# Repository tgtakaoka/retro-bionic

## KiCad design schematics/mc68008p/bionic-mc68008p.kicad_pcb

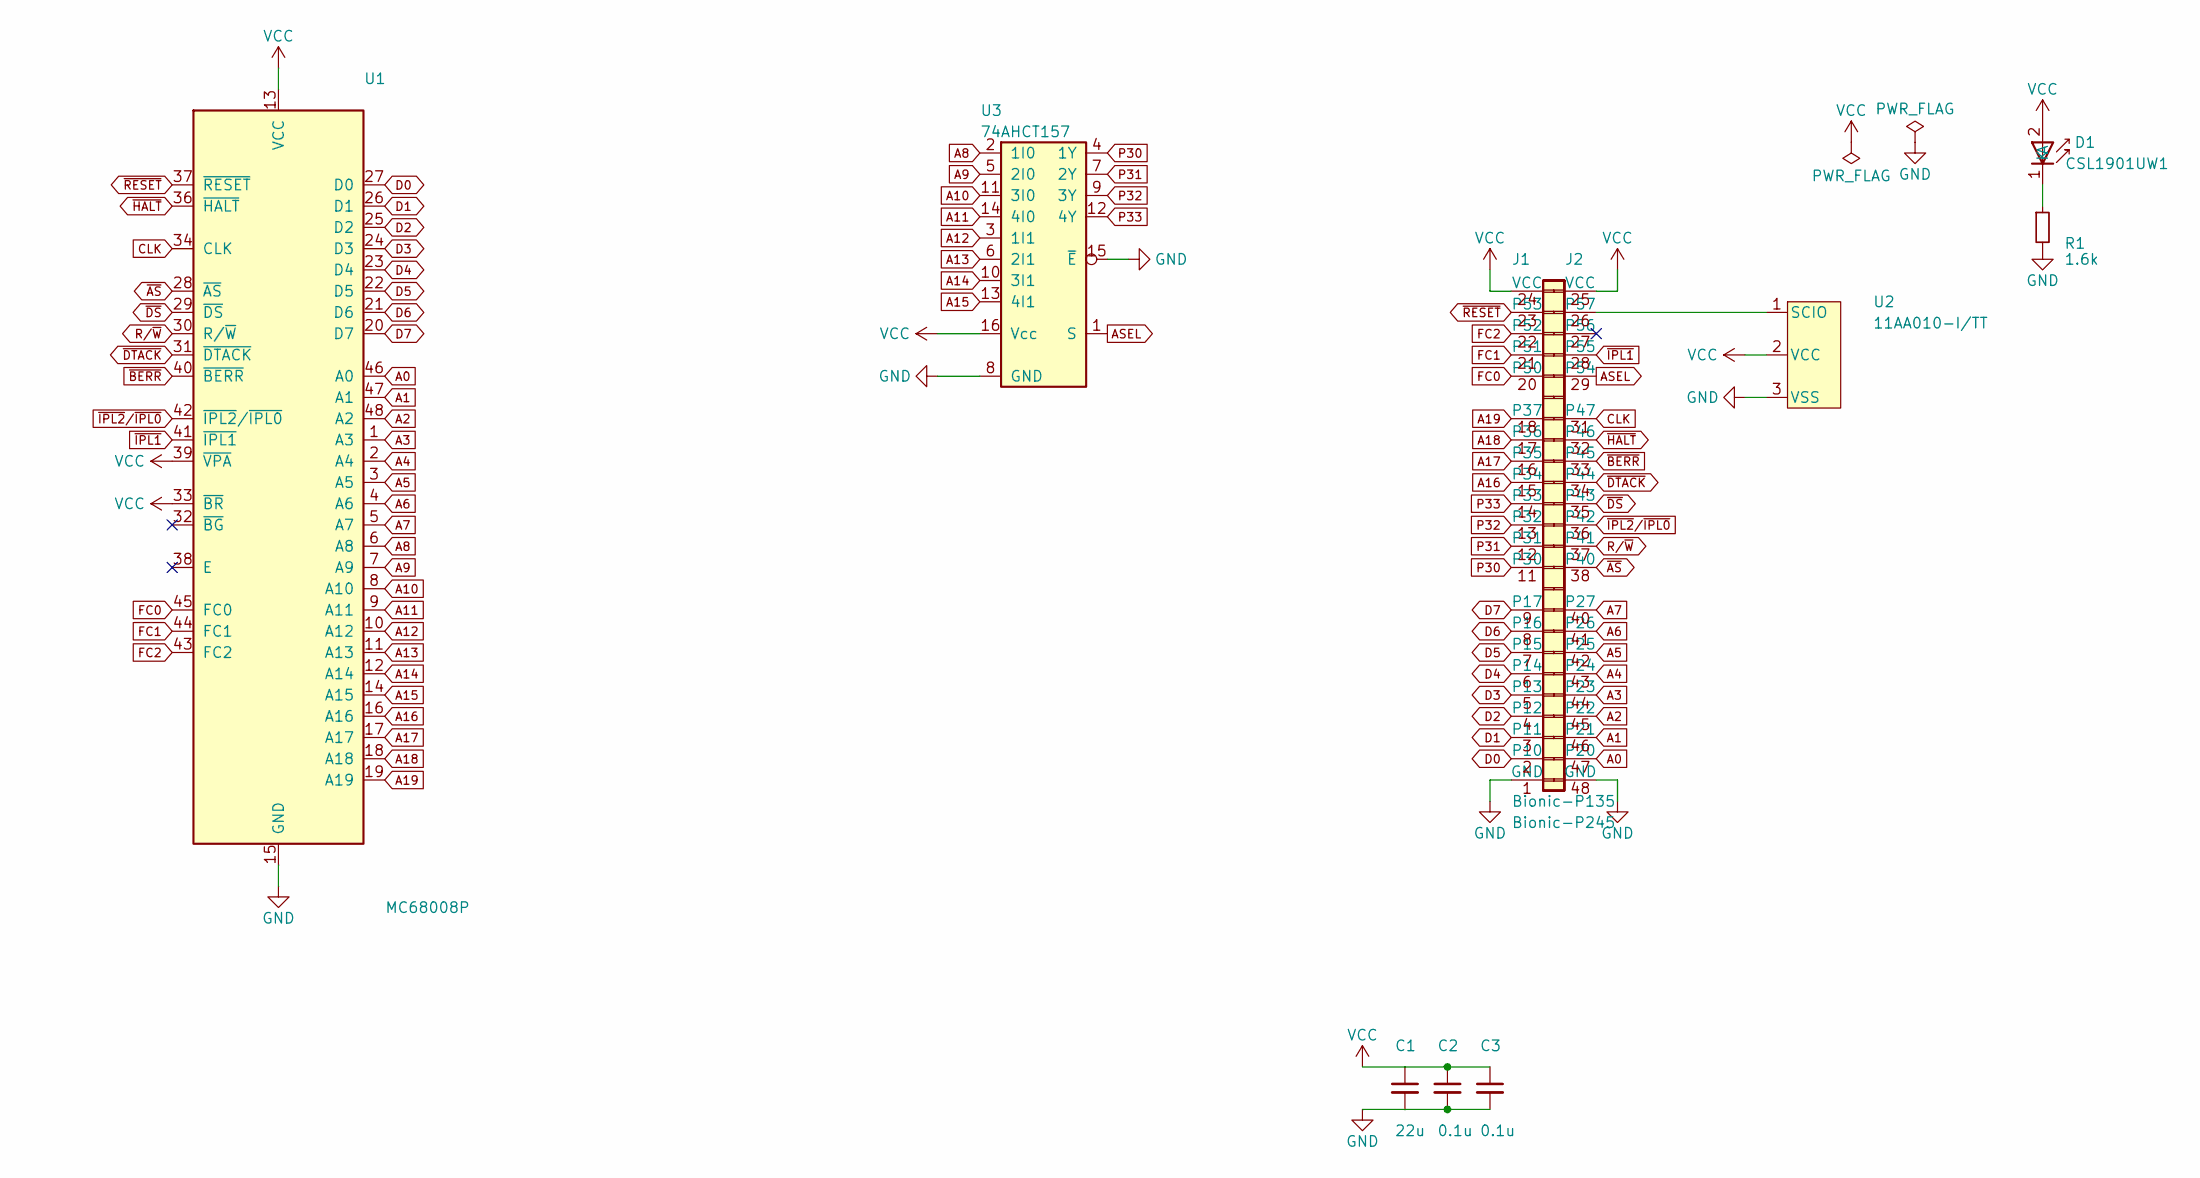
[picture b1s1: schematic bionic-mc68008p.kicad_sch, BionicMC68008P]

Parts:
C1: 22u; C_0603_1608Metric_Pad1.08x0.95mm_HandSolder
C2, C3: 0.1u; C_0603_1608Metric_Pad1.08x0.95mm_HandSolder
D1: CSL1901UW1; LED_CSL1901UW1_ROM-M
J1: Bionic-P135; Bionic-P135_SMT
J2: Bionic-P245; Bionic-P245_SMT
R1: 1.6k; R_0603_1608Metric_Pad0.98x0.95mm_HandSolder
U1: MC68008P; DIP-48_W15.24mm_Socket
U2: 11AA010-I/TT; SOT-23_MC_MCH-M
U3: 74AHCT157; PW16-M

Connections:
A0: J2.47 (P20), U1.46 (A0)
A1: J2.46 (P21), U1.47 (A1)
A2: J2.45 (P22), U1.48 (A2)
A3: J2.44 (P23), U1.1 (A3)
A4: J2.43 (P24), U1.2 (A4)
A5: J2.42 (P25), U1.3 (A5)
A6: J2.41 (P26), U1.4 (A6)
A7: J2.40 (P27), U1.5 (A7)
A8: U1.6 (A8), U3.2 (1I0)
A9: U1.7 (A9), U3.5 (2I0)
A10: U1.8 (A10), U3.11 (3I0)
A11: U1.9 (A11), U3.14 (4I0)
A12: U1.10 (A12), U3.3 (1I1)
A13: U1.11 (A13), U3.6 (2I1)
A14: U1.12 (A14), U3.10 (3I1)
A15: U1.14 (A15), U3.13 (4I1)
A16: J1.15 (P34), U1.16 (A16)
A17: J1.16 (P35), U1.17 (A17)
A18: J1.17 (P36), U1.18 (A18)
A19: J1.18 (P37), U1.19 (A19)
ASEL: J2.29 (P54), U3.1 (S)
CLK: J2.31 (P47), U1.34 (CLK)
D0: J1.2 (P10), U1.27 (D0)
D1: J1.3 (P11), U1.26 (D1)
D2: J1.4 (P12), U1.25 (D2)
D3: J1.5 (P13), U1.24 (D3)
D4: J1.6 (P14), U1.23 (D4)
D5: J1.7 (P15), U1.22 (D5)
D6: J1.8 (P16), U1.21 (D6)
D7: J1.9 (P17), U1.20 (D7)
FC0: J1.20 (P50), U1.45 (FC0)
FC1: J1.21 (P51), U1.44 (FC1)
FC2: J1.22 (P52), U1.43 (FC2)
GND: C1.2, C2.2, C3.2, J1.1 (GND), J2.48 (GND), R1.2, U1.15 (GND), U1.35 (GND), U2.3 (VSS), U3.8 (GND), U3.15 (~E)
unnamed: D1.1 (K), R1.1
unnamed: J2.26 (P57), U2.1 (SCIO)
P30: J1.11 (P30), U3.4 (1Y)
P31: J1.12 (P31), U3.7 (2Y)
P32: J1.13 (P32), U3.9 (3Y)
P33: J1.14 (P33), U3.12 (4Y)
R/~W: J2.37 (P41), U1.30 (R/~W)
VCC: C1.1, C2.1, C3.1, D1.2 (A), J1.24 (VCC), J2.25 (VCC), U1.13 (VCC), U1.33 (~BR), U1.39 (~VPA), U2.2 (VCC), U3.16 (Vcc)
~AS: J2.38 (P40), U1.28 (~AS)
~BERR: J2.33 (P45), U1.40 (~BERR)
~DS: J2.35 (P43), U1.29 (~DS)
~DTACK: J2.34 (P44), U1.31 (~DTACK)
~HALT: J2.32 (P46), U1.36 (~HALT)
~IPL1: J2.28 (P55), U1.41 (~IPL1)
~IPL2/~IPL0: J2.36 (P42), U1.42 (~IPL2/~IPL0)
~RESET: J1.23 (P53), U1.37 (~RESET)

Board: 2 copper layers, 10 parts (2 on the bottom side), 50 nets, no tracks yet.

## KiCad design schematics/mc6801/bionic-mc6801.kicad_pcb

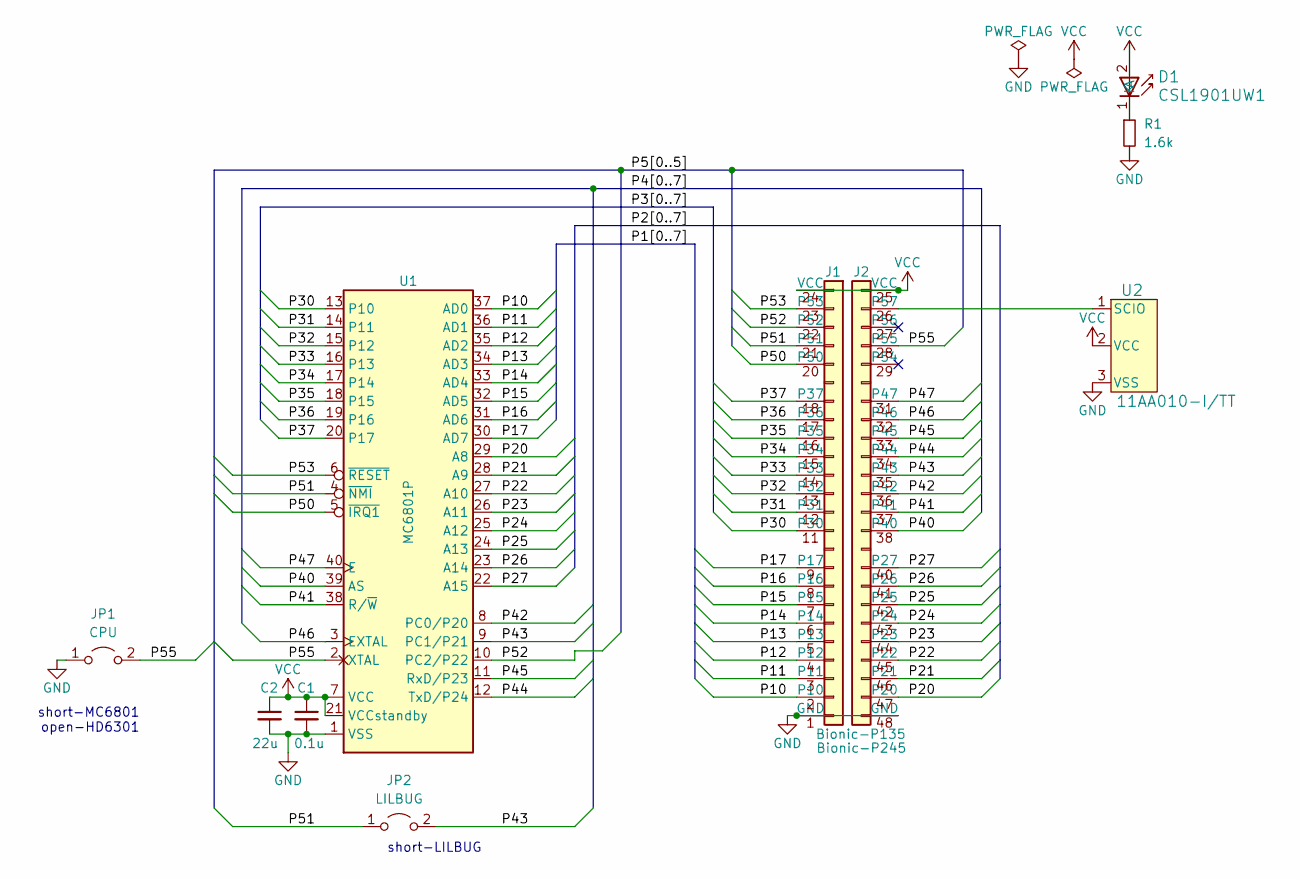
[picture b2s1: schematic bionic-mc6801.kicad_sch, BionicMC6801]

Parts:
C1: 0.1u; C_0603_1608Metric_Pad1.08x0.95mm_HandSolder
C2: 22u; C_0603_1608Metric_Pad1.08x0.95mm_HandSolder
D1: CSL1901UW1; LED_CSL1901UW1_ROM-M
J1: Bionic-P135; Bionic-P135_THT
J2: Bionic-P245; Bionic-P245_THT
JP1: CPU; SolderJumper-2_P1.3mm_Open_RoundedPad1.0x1.5mm
JP2: LILBUG; PinHeader_1x02_P2.54mm_Vertical
R1: 1.6k; R_0603_1608Metric_Pad0.98x0.95mm_HandSolder
U1: MC6801P; DIP-40_W15.24mm_Socket
U2: 11AA010-I/TT; SOT-23_MC_MCH-M

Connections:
/P10: J1.2 (P10), U1.37 (AD0)
/P11: J1.3 (P11), U1.36 (AD1)
/P12: J1.4 (P12), U1.35 (AD2)
/P13: J1.5 (P13), U1.34 (AD3)
/P14: J1.6 (P14), U1.33 (AD4)
/P15: J1.7 (P15), U1.32 (AD5)
/P16: J1.8 (P16), U1.31 (AD6)
/P17: J1.9 (P17), U1.30 (AD7)
/P20: J2.47 (P20), U1.29 (A8)
/P21: J2.46 (P21), U1.28 (A9)
/P22: J2.45 (P22), U1.27 (A10)
/P23: J2.44 (P23), U1.26 (A11)
/P24: J2.43 (P24), U1.25 (A12)
/P25: J2.42 (P25), U1.24 (A13)
/P26: J2.41 (P26), U1.23 (A14)
/P27: J2.40 (P27), U1.22 (A15)
/P30: J1.11 (P30), U1.13 (P10)
/P31: J1.12 (P31), U1.14 (P11)
/P32: J1.13 (P32), U1.15 (P12)
/P33: J1.14 (P33), U1.16 (P13)
/P34: J1.15 (P34), U1.17 (P14)
/P35: J1.16 (P35), U1.18 (P15)
/P36: J1.17 (P36), U1.19 (P16)
/P37: J1.18 (P37), U1.20 (P17)
/P40: J2.38 (P40), U1.39 (AS)
/P41: J2.37 (P41), U1.38 (R/~W)
/P42: J2.36 (P42), U1.8 (PC0/P20)
/P43: J2.35 (P43), JP2.2 (B), U1.9 (PC1/P21)
/P44: J2.34 (P44), U1.12 (TxD/P24)
/P45: J2.33 (P45), U1.11 (RxD/P23)
/P46: J2.32 (P46), U1.3 (EXTAL)
/P47: J2.31 (P47), U1.40 (E)
/P50: J1.20 (P50), U1.5 (~IRQ1)
/P51: J1.21 (P51), JP2.1 (A), U1.4 (~NMI)
/P52: J1.22 (P52), U1.10 (PC2/P22)
/P53: J1.23 (P53), U1.6 (~RESET)
/P55: J2.28 (P55), JP1.2 (B), U1.2 (XTAL)
GND: C1.2, C2.2, J1.1 (GND), J2.48 (GND), JP1.1 (A), R1.2, U1.1 (VSS), U2.3 (VSS)
unnamed: D1.1 (K), R1.1
unnamed: J2.26 (P57), U2.1 (SCIO)
VCC: C1.1, C2.1, D1.2 (A), J1.24 (VCC), J2.25 (VCC), U1.7 (VCC), U1.21 (VCCstandby), U2.2 (VCC)

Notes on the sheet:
short-MC6801 open-HD6301
short-LILBUG

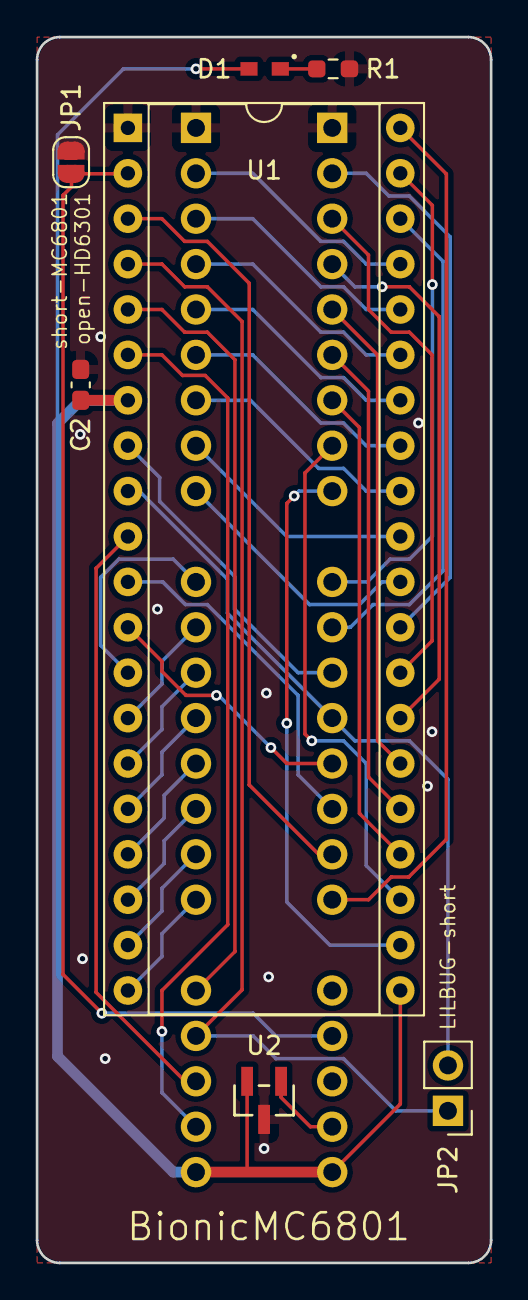
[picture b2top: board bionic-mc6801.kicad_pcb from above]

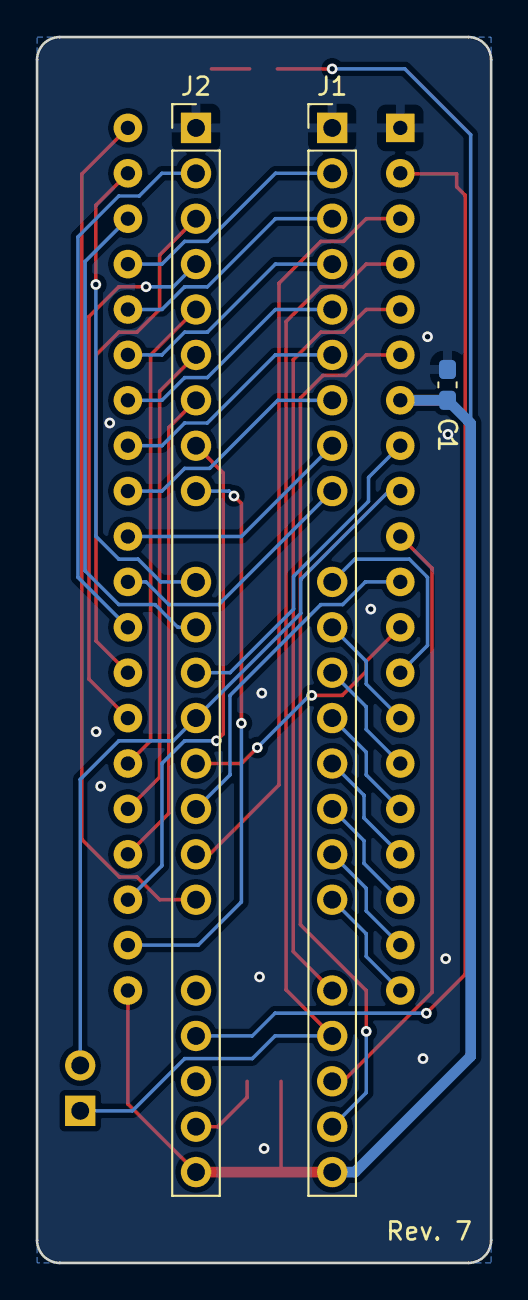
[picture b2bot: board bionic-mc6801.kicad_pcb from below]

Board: 2 copper layers, 25.4 x 68.6 mm, 10 parts (3 on the bottom side), 41 nets.

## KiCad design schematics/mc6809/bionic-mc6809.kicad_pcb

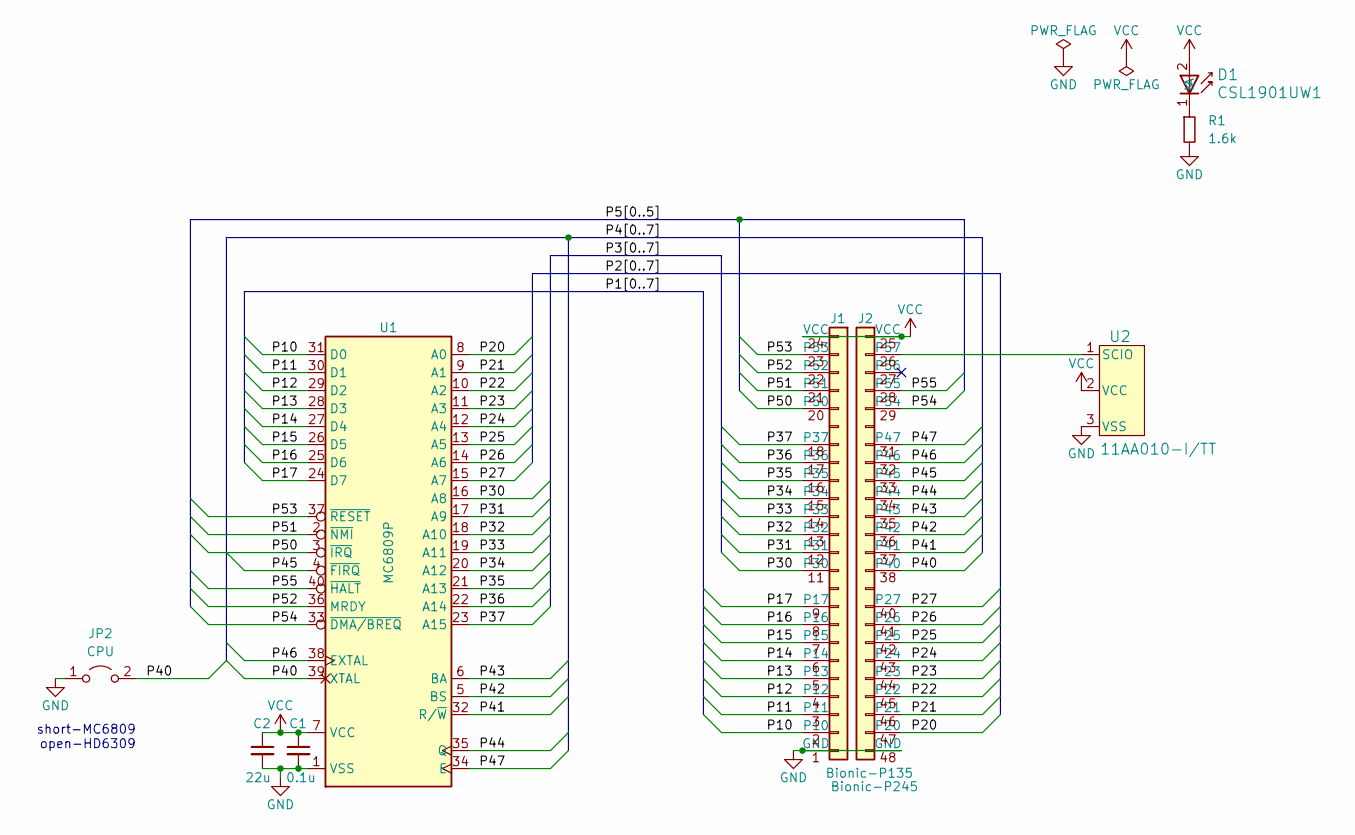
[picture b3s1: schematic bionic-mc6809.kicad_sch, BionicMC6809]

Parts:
C1: 0.1u; C_0603_1608Metric_Pad1.08x0.95mm_HandSolder
C2: 22u; C_0603_1608Metric_Pad1.08x0.95mm_HandSolder
D1: CSL1901UW1; LED_CSL1901UW1_ROM-M
J1: Bionic-P135; Bionic-P135_THT
J2: Bionic-P245; Bionic-P245_THT
JP2: CPU; SolderJumper-2_P1.3mm_Open_RoundedPad1.0x1.5mm
R1: 1.6k; R_0603_1608Metric_Pad0.98x0.95mm_HandSolder
U1: MC6809P; DIP-40_W15.24mm_Socket
U2: 11AA010-I/TT; SOT-23_MC_MCH-M

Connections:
/P10: J1.2 (P10), U1.31 (D0)
/P11: J1.3 (P11), U1.30 (D1)
/P12: J1.4 (P12), U1.29 (D2)
/P13: J1.5 (P13), U1.28 (D3)
/P14: J1.6 (P14), U1.27 (D4)
/P15: J1.7 (P15), U1.26 (D5)
/P16: J1.8 (P16), U1.25 (D6)
/P17: J1.9 (P17), U1.24 (D7)
/P20: J2.47 (P20), U1.8 (A0)
/P21: J2.46 (P21), U1.9 (A1)
/P22: J2.45 (P22), U1.10 (A2)
/P23: J2.44 (P23), U1.11 (A3)
/P24: J2.43 (P24), U1.12 (A4)
/P25: J2.42 (P25), U1.13 (A5)
/P26: J2.41 (P26), U1.14 (A6)
/P27: J2.40 (P27), U1.15 (A7)
/P30: J1.11 (P30), U1.16 (A8)
/P31: J1.12 (P31), U1.17 (A9)
/P32: J1.13 (P32), U1.18 (A10)
/P33: J1.14 (P33), U1.19 (A11)
/P34: J1.15 (P34), U1.20 (A12)
/P35: J1.16 (P35), U1.21 (A13)
/P36: J1.17 (P36), U1.22 (A14)
/P37: J1.18 (P37), U1.23 (A15)
/P40: J2.38 (P40), JP2.2 (B), U1.39 (XTAL)
/P41: J2.37 (P41), U1.32 (R/~W)
/P42: J2.36 (P42), U1.5 (BS)
/P43: J2.35 (P43), U1.6 (BA)
/P44: J2.34 (P44), U1.35 (Q)
/P45: J2.33 (P45), U1.4 (~FIRQ)
/P46: J2.32 (P46), U1.38 (EXTAL)
/P47: J2.31 (P47), U1.34 (E)
/P50: J1.20 (P50), U1.3 (~IRQ)
/P51: J1.21 (P51), U1.2 (~NMI)
/P52: J1.22 (P52), U1.36 (MRDY)
/P53: J1.23 (P53), U1.37 (~RESET)
/P54: J2.29 (P54), U1.33 (~DMA/BREQ)
/P55: J2.28 (P55), U1.40 (~HALT)
GND: C1.2, C2.2, J1.1 (GND), J2.48 (GND), JP2.1 (A), R1.2, U1.1 (VSS), U2.3 (VSS)
unnamed: D1.1 (K), R1.1
unnamed: J2.26 (P57), U2.1 (SCIO)
VCC: C1.1, C2.1, D1.2 (A), J1.24 (VCC), J2.25 (VCC), U1.7 (VCC), U2.2 (VCC)

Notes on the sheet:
short-MC6809 open-HD6309

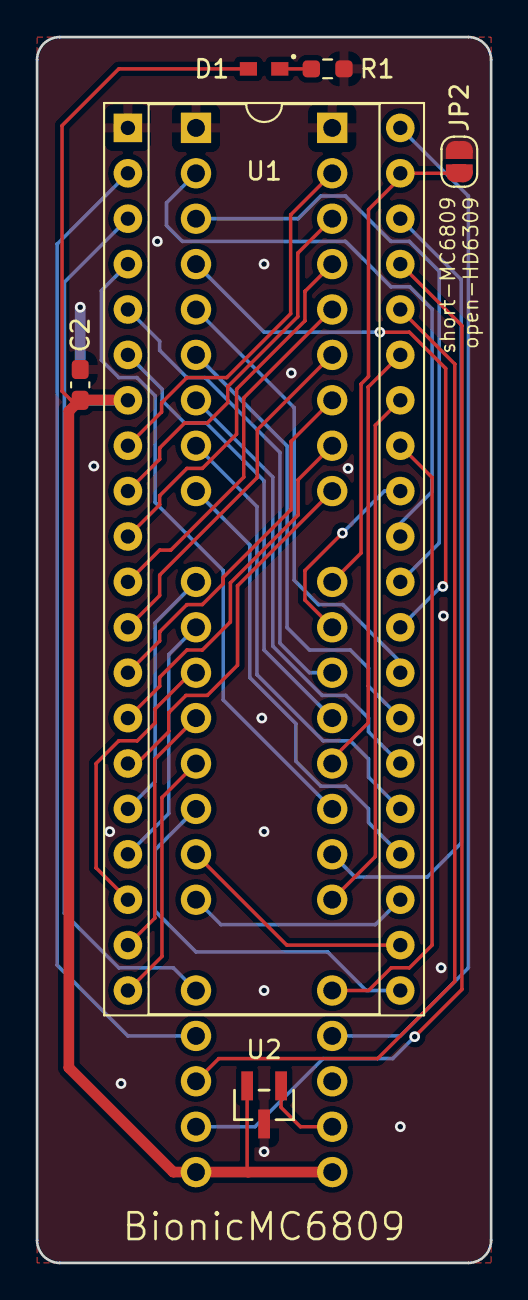
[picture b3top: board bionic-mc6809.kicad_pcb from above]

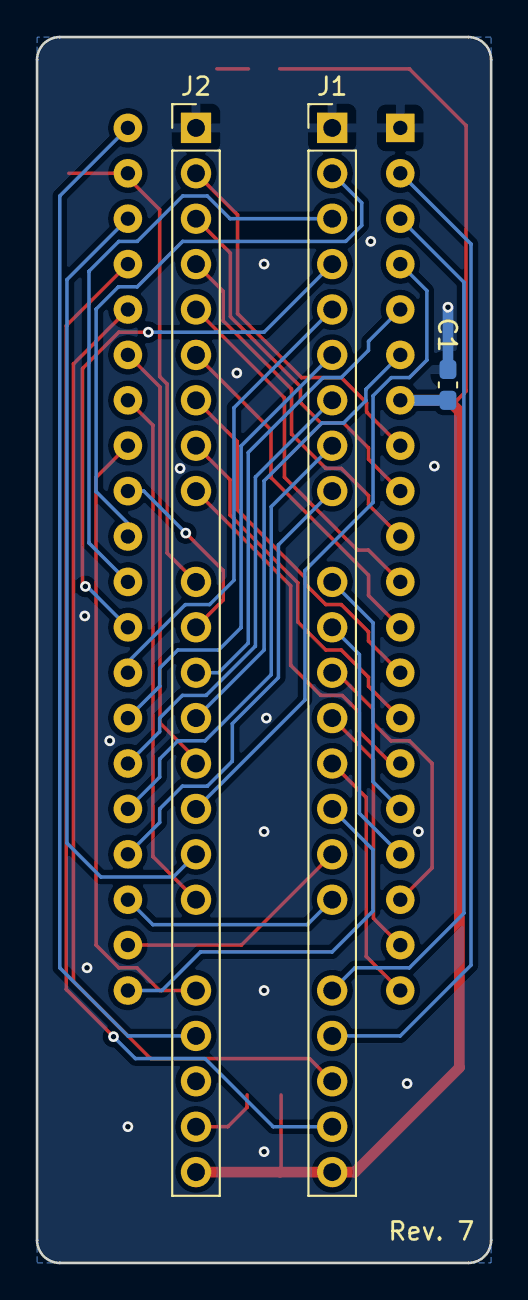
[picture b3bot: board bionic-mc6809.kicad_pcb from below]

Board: 2 copper layers, 25.4 x 68.6 mm, 9 parts (3 on the bottom side), 42 nets.

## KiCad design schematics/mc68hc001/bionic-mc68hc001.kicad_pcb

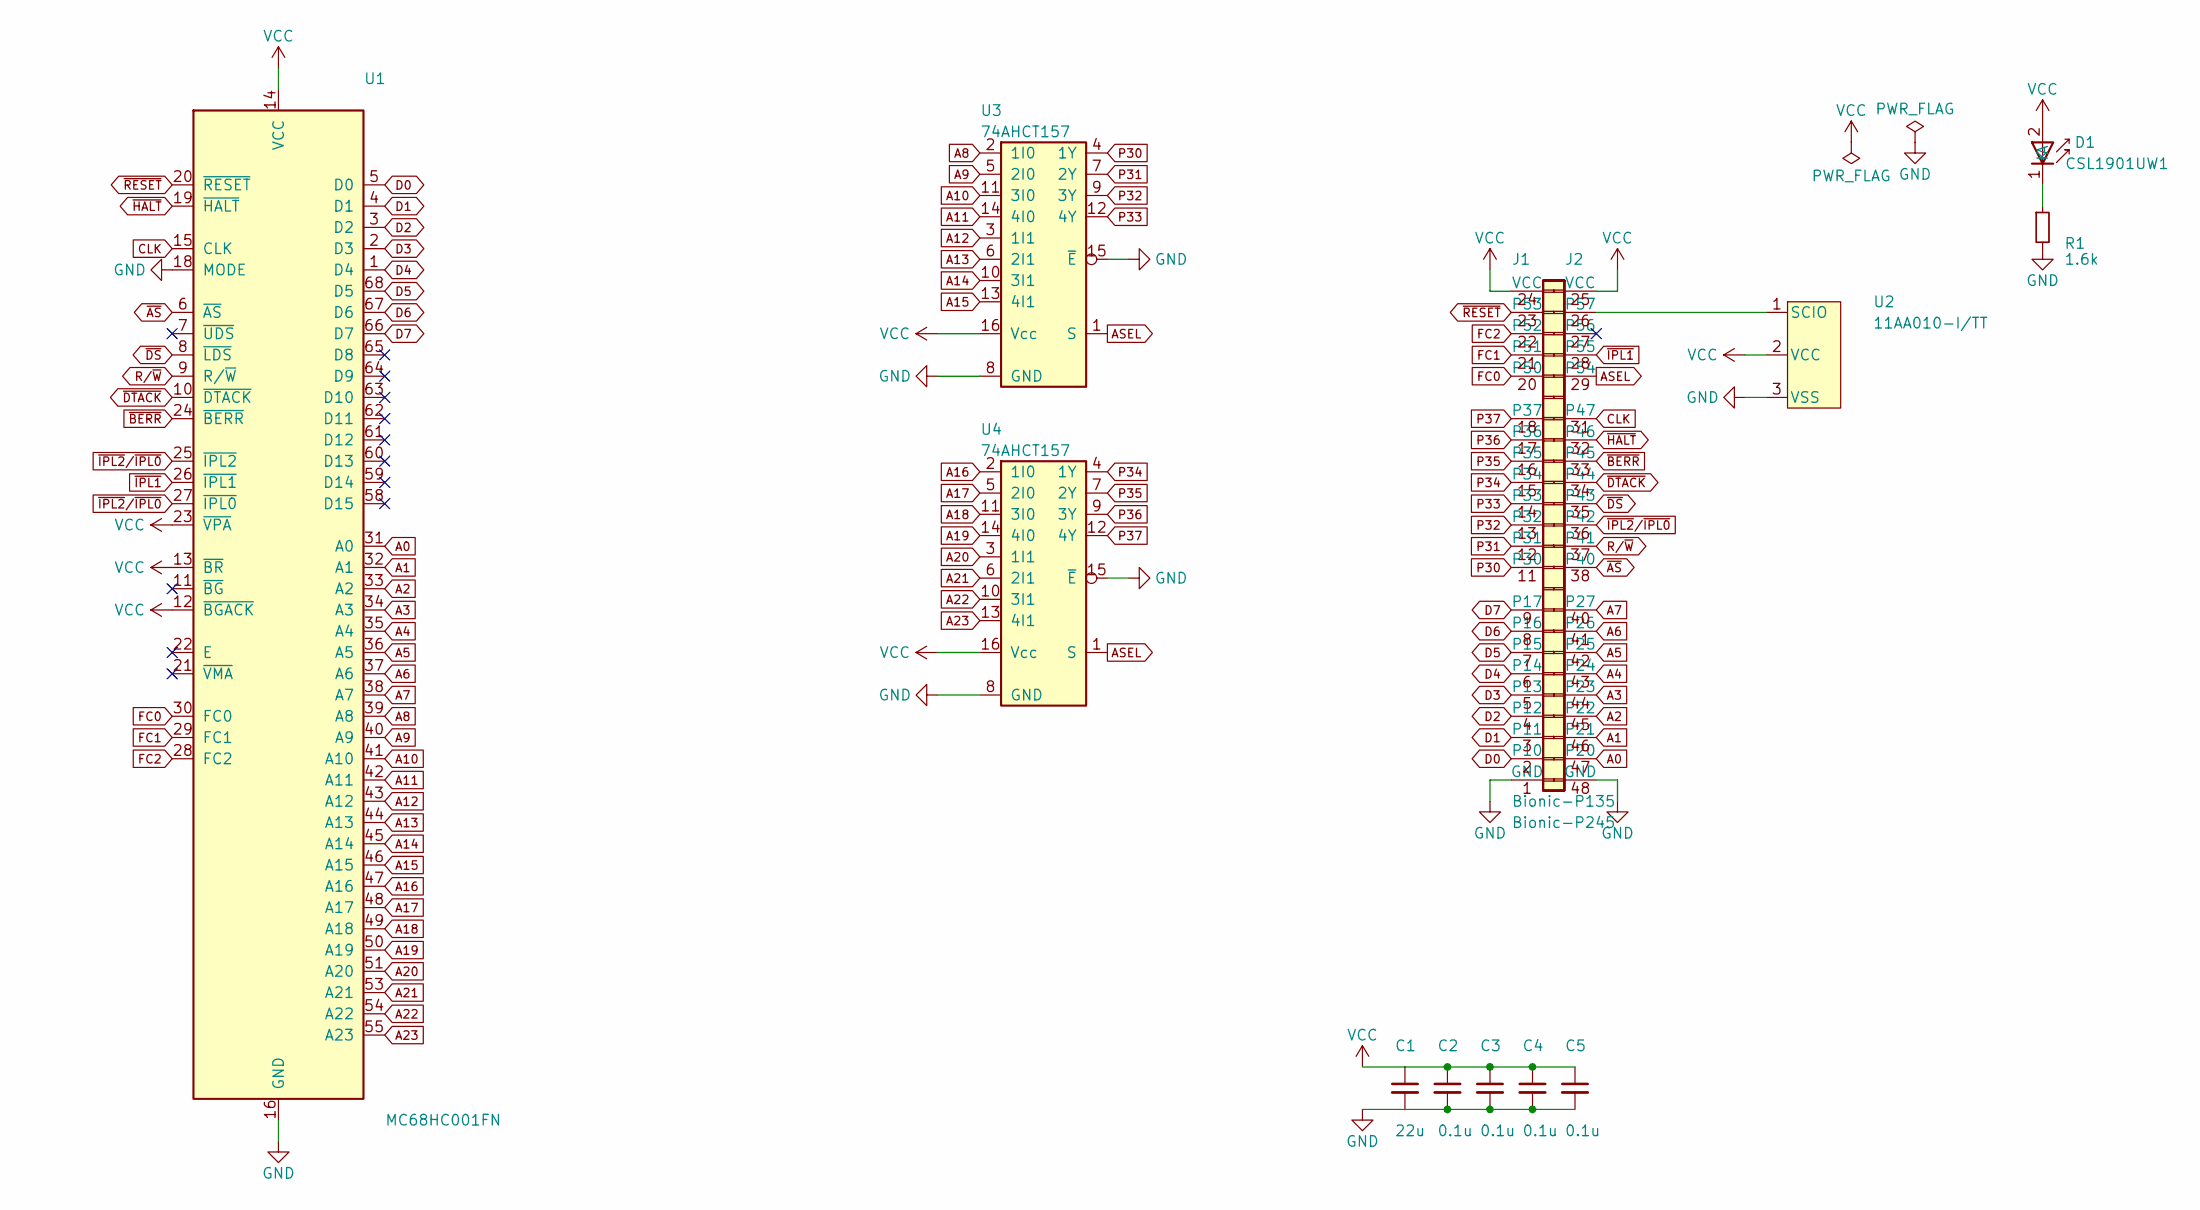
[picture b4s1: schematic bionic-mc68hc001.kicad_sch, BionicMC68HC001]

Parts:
C1: 22u; C_0603_1608Metric_Pad1.08x0.95mm_HandSolder
C2, C3, C4, C5: 0.1u; C_0603_1608Metric_Pad1.08x0.95mm_HandSolder
D1: CSL1901UW1; LED_CSL1901UW1_ROM-M
J1: Bionic-P135; Bionic-P135_SMT
J2: Bionic-P245; Bionic-P245_SMT
R1: 1.6k; R_0603_1608Metric_Pad0.98x0.95mm_HandSolder
U1: MC68HC001FN; PLCC-68_SMD-Socket
U2: 11AA010-I/TT; SOT-23_MC_MCH-M
U3, U4: 74AHCT157; PW16-M

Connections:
A0: J2.47 (P20), U1.31 (A0)
A1: J2.46 (P21), U1.32 (A1)
A2: J2.45 (P22), U1.33 (A2)
A3: J2.44 (P23), U1.34 (A3)
A4: J2.43 (P24), U1.35 (A4)
A5: J2.42 (P25), U1.36 (A5)
A6: J2.41 (P26), U1.37 (A6)
A7: J2.40 (P27), U1.38 (A7)
A8: U1.39 (A8), U3.2 (1I0)
A9: U1.40 (A9), U3.5 (2I0)
A10: U1.41 (A10), U3.11 (3I0)
A11: U1.42 (A11), U3.14 (4I0)
A12: U1.43 (A12), U3.3 (1I1)
A13: U1.44 (A13), U3.6 (2I1)
A14: U1.45 (A14), U3.10 (3I1)
A15: U1.46 (A15), U3.13 (4I1)
A16: U1.47 (A16), U4.2 (1I0)
A17: U1.48 (A17), U4.5 (2I0)
A18: U1.49 (A18), U4.11 (3I0)
A19: U1.50 (A19), U4.14 (4I0)
A20: U1.51 (A20), U4.3 (1I1)
A21: U1.53 (A21), U4.6 (2I1)
A22: U1.54 (A22), U4.10 (3I1)
A23: U1.55 (A23), U4.13 (4I1)
ASEL: J2.29 (P54), U3.1 (S), U4.1 (S)
CLK: J2.31 (P47), U1.15 (CLK)
D0: J1.2 (P10), U1.5 (D0)
D1: J1.3 (P11), U1.4 (D1)
D2: J1.4 (P12), U1.3 (D2)
D3: J1.5 (P13), U1.2 (D3)
D4: J1.6 (P14), U1.1 (D4)
D5: J1.7 (P15), U1.68 (D5)
D6: J1.8 (P16), U1.67 (D6)
D7: J1.9 (P17), U1.66 (D7)
FC0: J1.20 (P50), U1.30 (FC0)
FC1: J1.21 (P51), U1.29 (FC1)
FC2: J1.22 (P52), U1.28 (FC2)
GND: C1.2, C2.2, C3.2, C4.2, C5.2, J1.1 (GND), J2.48 (GND), R1.2, U1.16 (GND), U1.17 (GND), U1.18 (MODE), U1.56 (GND), U1.57 (GND), U2.3 (VSS), U3.8 (GND), U3.15 (~E), U4.8 (GND), U4.15 (~E)
unnamed: D1.1 (K), R1.1
unnamed: J2.26 (P57), U2.1 (SCIO)
P30: J1.11 (P30), U3.4 (1Y)
P31: J1.12 (P31), U3.7 (2Y)
P32: J1.13 (P32), U3.9 (3Y)
P33: J1.14 (P33), U3.12 (4Y)
P34: J1.15 (P34), U4.4 (1Y)
P35: J1.16 (P35), U4.7 (2Y)
P36: J1.17 (P36), U4.9 (3Y)
P37: J1.18 (P37), U4.12 (4Y)
R/~W: J2.37 (P41), U1.9 (R/~W)
VCC: C1.1, C2.1, C3.1, C4.1, C5.1, D1.2 (A), J1.24 (VCC), J2.25 (VCC), U1.12 (~BGACK), U1.13 (~BR), U1.14 (VCC), U1.23 (~VPA), U1.52 (VCC), U2.2 (VCC), U3.16 (Vcc), U4.16 (Vcc)
~AS: J2.38 (P40), U1.6 (~AS)
~BERR: J2.33 (P45), U1.24 (~BERR)
~DS: J2.35 (P43), U1.8 (~LDS)
~DTACK: J2.34 (P44), U1.10 (~DTACK)
~HALT: J2.32 (P46), U1.19 (~HALT)
~IPL1: J2.28 (P55), U1.26 (~IPL1)
~IPL2/~IPL0: J2.36 (P42), U1.25 (~IPL2), U1.27 (~IPL0)
~RESET: J1.23 (P53), U1.20 (~RESET)

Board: 2 copper layers, 13 parts (2 on the bottom side), 58 nets, no tracks yet.

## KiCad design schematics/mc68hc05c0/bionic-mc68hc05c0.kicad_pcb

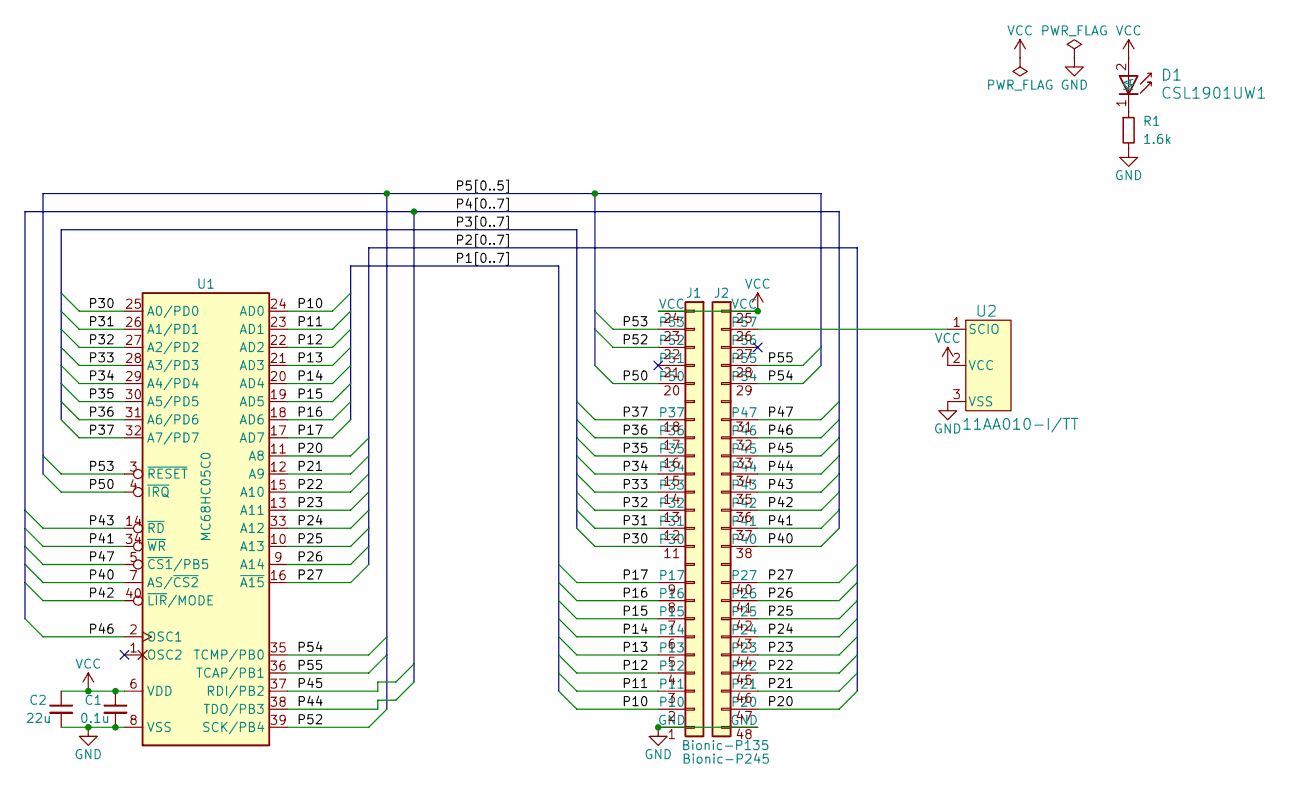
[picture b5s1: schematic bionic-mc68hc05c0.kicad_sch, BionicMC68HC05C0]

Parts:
C1: 0.1u; C_0603_1608Metric_Pad1.08x0.95mm_HandSolder
C2: 22u; C_0603_1608Metric_Pad1.08x0.95mm_HandSolder
D1: CSL1901UW1; LED_CSL1901UW1_ROM-M
J1: Bionic-P135; Bionic-P135_THT
J2: Bionic-P245; Bionic-P245_THT
R1: 1.6k; R_0603_1608Metric_Pad0.98x0.95mm_HandSolder
U1: MC68HC05C0; DIP-40_W15.24mm_Socket
U2: 11AA010-I/TT; SOT-23_MC_MCH-M

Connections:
/P10: J1.2 (P10), U1.24 (AD0)
/P11: J1.3 (P11), U1.23 (AD1)
/P12: J1.4 (P12), U1.22 (AD2)
/P13: J1.5 (P13), U1.21 (AD3)
/P14: J1.6 (P14), U1.20 (AD4)
/P15: J1.7 (P15), U1.19 (AD5)
/P16: J1.8 (P16), U1.18 (AD6)
/P17: J1.9 (P17), U1.17 (AD7)
/P20: J2.47 (P20), U1.11 (A8)
/P21: J2.46 (P21), U1.12 (A9)
/P22: J2.45 (P22), U1.15 (A10)
/P23: J2.44 (P23), U1.13 (A11)
/P24: J2.43 (P24), U1.33 (A12)
/P25: J2.42 (P25), U1.10 (A13)
/P26: J2.41 (P26), U1.9 (A14)
/P27: J2.40 (P27), U1.16 (~A15)
/P30: J1.11 (P30), U1.25 (A0/PD0)
/P31: J1.12 (P31), U1.26 (A1/PD1)
/P32: J1.13 (P32), U1.27 (A2/PD2)
/P33: J1.14 (P33), U1.28 (A3/PD3)
/P34: J1.15 (P34), U1.29 (A4/PD4)
/P35: J1.16 (P35), U1.30 (A5/PD5)
/P36: J1.17 (P36), U1.31 (A6/PD6)
/P37: J1.18 (P37), U1.32 (A7/PD7)
/P40: J2.38 (P40), U1.7 (AS/~CS2)
/P41: J2.37 (P41), U1.34 (~WR)
/P42: J2.36 (P42), U1.40 (~LIR/MODE)
/P43: J2.35 (P43), U1.14 (~RD)
/P44: J2.34 (P44), U1.38 (TDO/PB3)
/P45: J2.33 (P45), U1.37 (RDI/PB2)
/P46: J2.32 (P46), U1.2 (OSC1)
/P47: J2.31 (P47), U1.5 (~CS1/PB5)
/P50: J1.20 (P50), U1.4 (~IRQ)
/P52: J1.22 (P52), U1.39 (SCK/PB4)
/P53: J1.23 (P53), U1.3 (~RESET)
/P54: J2.29 (P54), U1.35 (TCMP/PB0)
/P55: J2.28 (P55), U1.36 (TCAP/PB1)
GND: C1.2, C2.2, J1.1 (GND), J2.48 (GND), R1.2, U1.8 (VSS), U2.3 (VSS)
unnamed: D1.1 (K), R1.1
unnamed: J2.26 (P57), U2.1 (SCIO)
VCC: C1.1, C2.1, D1.2 (A), J1.24 (VCC), J2.25 (VCC), U1.6 (VDD), U2.2 (VCC)

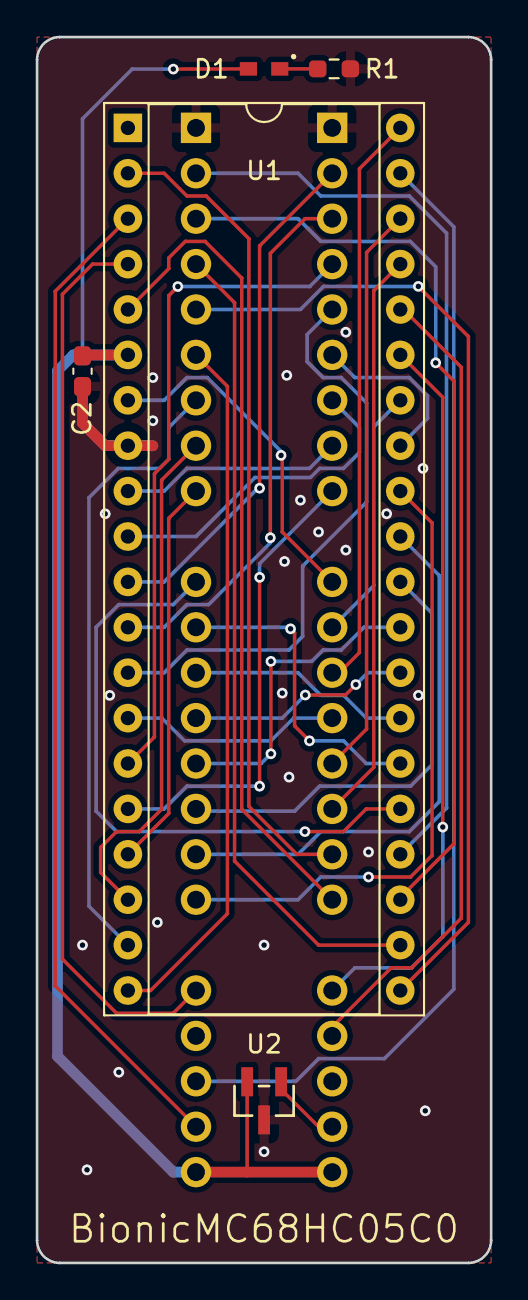
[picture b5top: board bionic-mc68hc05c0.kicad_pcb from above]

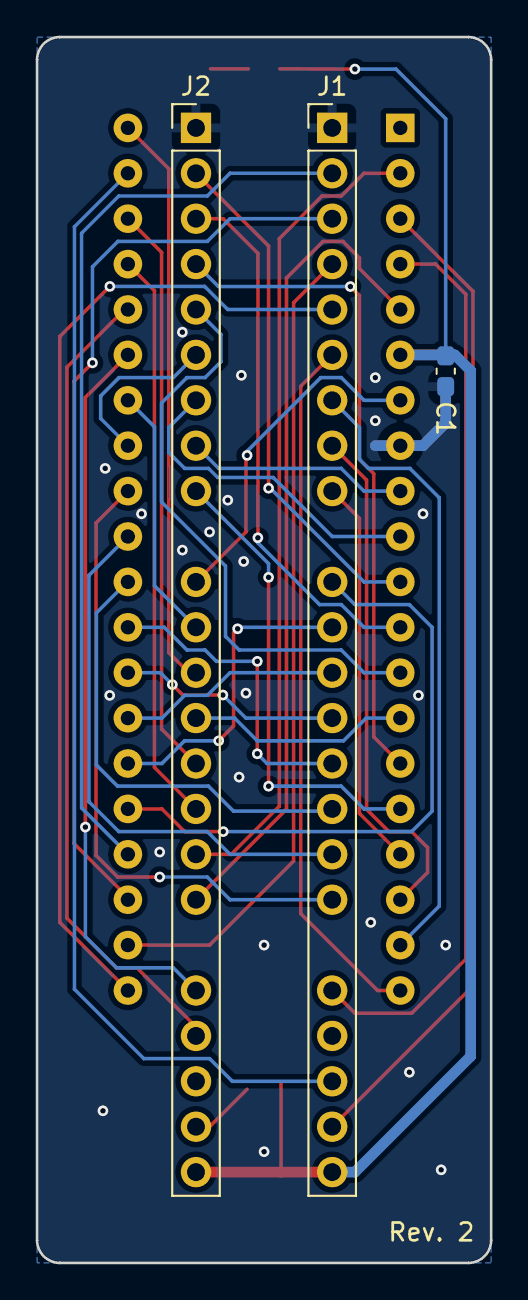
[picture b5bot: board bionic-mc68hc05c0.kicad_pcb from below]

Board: 2 copper layers, 25.4 x 68.6 mm, 8 parts (3 on the bottom side), 41 nets.

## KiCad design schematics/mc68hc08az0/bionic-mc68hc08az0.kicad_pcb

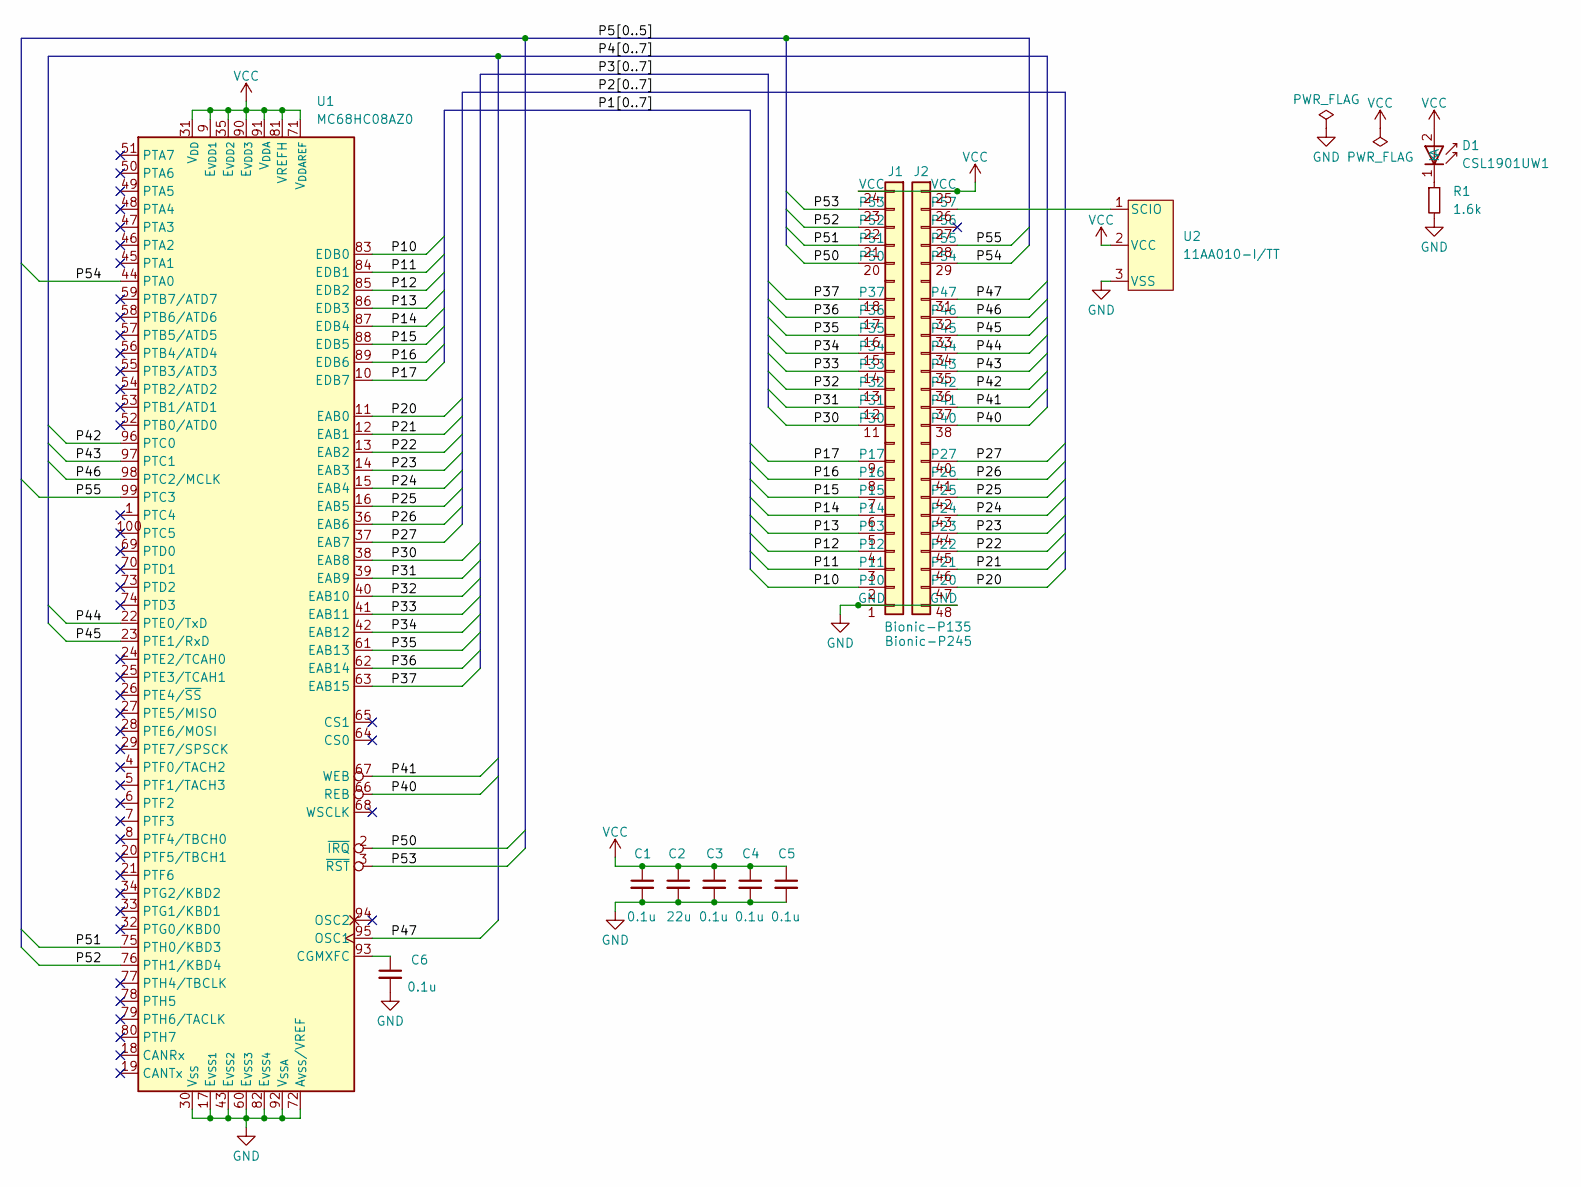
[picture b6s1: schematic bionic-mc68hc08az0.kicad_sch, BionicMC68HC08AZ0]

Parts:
C1, C3, C4, C5, C6: 0.1u; C_0603_1608Metric_Pad1.08x0.95mm_HandSolder
C2: 22u; C_0603_1608Metric_Pad1.08x0.95mm_HandSolder
D1: CSL1901UW1; LED_CSL1901UW1_ROM-M
J1: Bionic-P135; Bionic-P135_SMT
J2: Bionic-P245; Bionic-P245_SMT
R1: 1.6k; R_0603_1608Metric_Pad0.98x0.95mm_HandSolder
U1: MC68HC08AZ0; LQFP-100_14x14mm_P0.5mm
U2: 11AA010-I/TT; SOT-23_MC_MCH-M

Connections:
/P10: J1.2 (P10), U1.83 (EDB0)
/P11: J1.3 (P11), U1.84 (EDB1)
/P12: J1.4 (P12), U1.85 (EDB2)
/P13: J1.5 (P13), U1.86 (EDB3)
/P14: J1.6 (P14), U1.87 (EDB4)
/P15: J1.7 (P15), U1.88 (EDB5)
/P16: J1.8 (P16), U1.89 (EDB6)
/P17: J1.9 (P17), U1.10 (EDB7)
/P20: J2.47 (P20), U1.11 (EAB0)
/P21: J2.46 (P21), U1.12 (EAB1)
/P22: J2.45 (P22), U1.13 (EAB2)
/P23: J2.44 (P23), U1.14 (EAB3)
/P24: J2.43 (P24), U1.15 (EAB4)
/P25: J2.42 (P25), U1.16 (EAB5)
/P26: J2.41 (P26), U1.36 (EAB6)
/P27: J2.40 (P27), U1.37 (EAB7)
/P30: J1.11 (P30), U1.38 (EAB8)
/P31: J1.12 (P31), U1.39 (EAB9)
/P32: J1.13 (P32), U1.40 (EAB10)
/P33: J1.14 (P33), U1.41 (EAB11)
/P34: J1.15 (P34), U1.42 (EAB12)
/P35: J1.16 (P35), U1.61 (EAB13)
/P36: J1.17 (P36), U1.62 (EAB14)
/P37: J1.18 (P37), U1.63 (EAB15)
/P40: J2.38 (P40), U1.66 (REB)
/P41: J2.37 (P41), U1.67 (WEB)
/P42: J2.36 (P42), U1.96 (PTC0)
/P43: J2.35 (P43), U1.97 (PTC1)
/P44: J2.34 (P44), U1.22 (PTE0/TxD)
/P45: J2.33 (P45), U1.23 (PTE1/RxD)
/P46: J2.32 (P46), U1.98 (PTC2/MCLK)
/P47: J2.31 (P47), U1.95 (OSC1)
/P50: J1.20 (P50), U1.2 (~IRQ)
/P51: J1.21 (P51), U1.75 (PTH0/KBD3)
/P52: J1.22 (P52), U1.76 (PTH1/KBD4)
/P53: J1.23 (P53), U1.3 (~RST)
/P54: J2.29 (P54), U1.44 (PTA0)
/P55: J2.28 (P55), U1.99 (PTC3)
GND: C1.2, C2.2, C3.2, C4.2, C5.2, C6.2, J1.1 (GND), J2.48 (GND), R1.2, U1.17 (EVSS1), U1.30 (VSS), U1.43 (EVSS2), U1.60 (EVSS3), U1.72 (AVSS/VREFL), U1.82 (EVSS4), U1.92 (VSSA), U2.3 (VSS)
unnamed: D1.1 (K), R1.1
unnamed: J2.26 (P57), U2.1 (SCIO)
unnamed: C6.1, U1.93 (CGMXFC)
VCC: C1.1, C2.1, C3.1, C4.1, C5.1, D1.2 (A), J1.24 (VCC), J2.25 (VCC), U1.9 (EVDD1), U1.31 (VDD), U1.35 (EVDD2), U1.71 (VDDAREF), U1.81 (VREFH), U1.90 (EVDD3), U1.91 (VDDA), U2.2 (VCC)
